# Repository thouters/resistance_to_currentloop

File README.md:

3-wire current loop transmitter 4-20mA
======================================

Design files of https://www.thouters.be/RainWaterTankLevelSensor.html

- two_terminal_current_source contains a resistance to 4-20mA current loop converter
- principle contains some simplifications
- two_terminal_ladder a simple reed ladder
- three_terminal_ladder a reed ladder with interleaved tap points

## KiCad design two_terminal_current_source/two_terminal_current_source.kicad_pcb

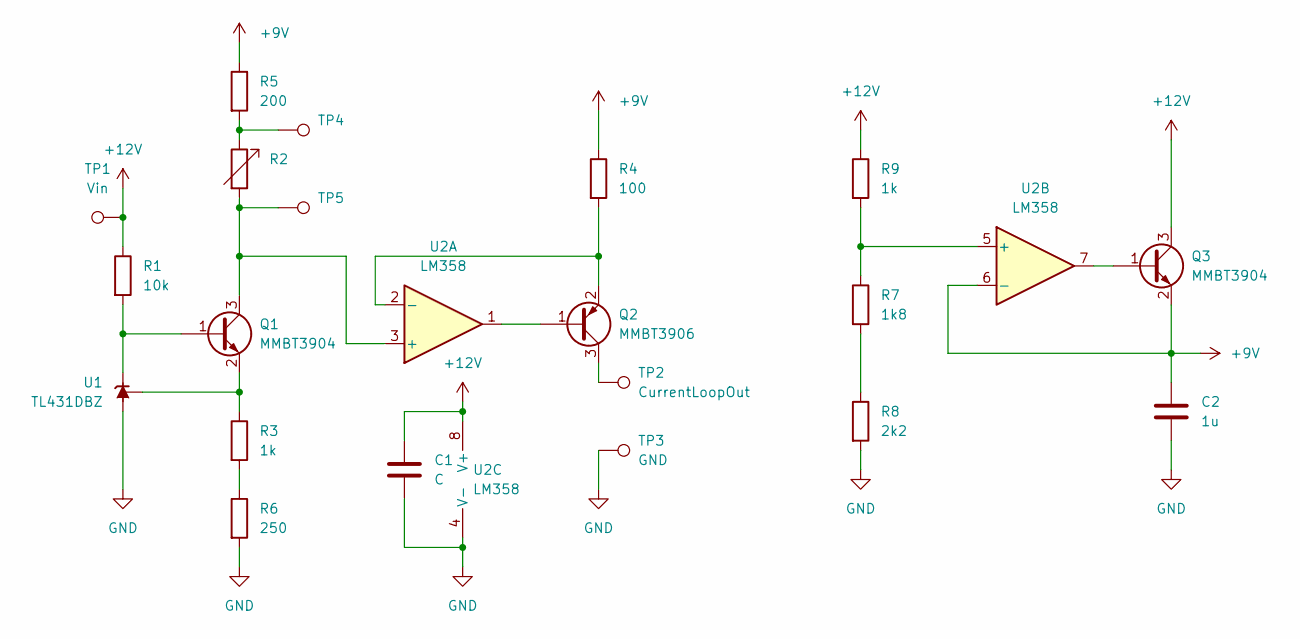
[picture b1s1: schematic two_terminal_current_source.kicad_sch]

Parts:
C1: C; C_0603_1608Metric_Pad1.08x0.95mm_HandSolder
C2: 1u; C_0603_1608Metric_Pad1.08x0.95mm_HandSolder
Q1, Q3: MMBT3904; SOT-23_Handsoldering
Q2: MMBT3906; SOT-23_Handsoldering
R1: 10k; R_0603_1608Metric
R2: (no value)
R3, R9: 1k; R_0603_1608Metric
R4: 100; R_0603_1608Metric
R5: 200; R_0603_1608Metric
R6: 250; R_0603_1608Metric
R7: 1k8; R_0603_1608Metric
R8: 2k2; R_0603_1608Metric
TP1: Vin; PinHeader_1x01_P2.54mm_Vertical
TP2: CurrentLoopOut; PinHeader_1x01_P2.54mm_Vertical
TP3: GND; PinHeader_1x01_P2.54mm_Vertical
TP4, TP5: PinHeader_1x01_P2.54mm_Vertical
U1: TL431DBZ; SOT-23
U2: LM358; SO-8_5.3x6.2mm_P1.27mm

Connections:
+9V: C2.1, Q3.2 (E), R4.1, R5.1, U2.6 (-)
+12V: C1.1, Q3.3 (C), R1.1, R9.1, TP1.1, U2.8 (V+)
GND: C1.2, C2.2, R6.2, R8.2, TP3.1, U1.3 (A), U2.4 (V-)
unnamed: Q1.1 (B), R1.2, U1.1 (K)
unnamed: Q1.2 (E), R3.1, U1.2 (REF)
unnamed: Q1.3 (C), R2.2, TP5.1, U2.3 (+)
unnamed: Q2.1 (B), U2.1
unnamed: Q2.2 (E), R4.2, U2.2 (-)
unnamed: Q2.3 (C), TP2.1
unnamed: Q3.1 (B), U2.7
unnamed: R2.1, R5.2, TP4.1
unnamed: R3.2, R6.1
unnamed: R7.1, R9.2, U2.5 (+)
unnamed: R7.2, R8.1

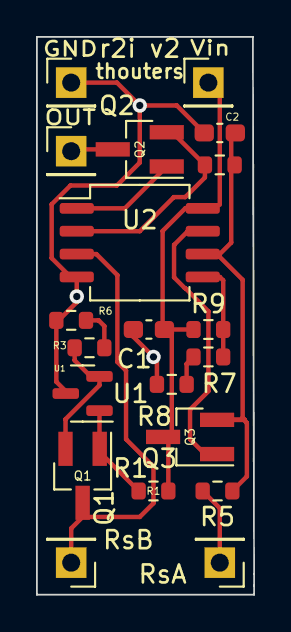
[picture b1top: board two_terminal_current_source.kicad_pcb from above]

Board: 2 copper layers, 12.1 x 31.0 mm, 20 parts (0 on the bottom side), 14 nets.

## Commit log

2022-08-06 revision 0
2022-08-18 move around schematic components
2022-08-18 Add readme and other files
2022-08-31 Move connectors, fix silkscreen, add identifier
    * Move output to left side to suit mechanical enclosure
    * Move sense resistor input pads to side of board to suit mechanical enclosure
    * Move more component identifiers to silkscreen layer
    * Add board version, identification
